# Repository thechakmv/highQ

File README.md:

# Pressure Sensor Signal Conditioning PCB

## Overview
A Schematic for the Amphenol NPH-8-200AH pressure sensor for use in aircraft systems. The circuit measures, amplifies, and filters the bridge output of the sensor to produce an analog voltage signal.

Circuit Schematic was designed to withstand noisy RF Radiation, and noise from the power of the plane itself.

## System Architecture

### Assumptions made:
- 5V & 12V Power rails
- Operating Freq ~ 30Hz (Should be sufficent for just pressure readings)

## Signal Chain

### 1. LT3092 Current Source
Current source designed to give consistent excitation current to the NPH-8-200AH
- 50ppm/C, so very temperature resistant
- Iout = 10uA * (Rset/Rout)
- R set = 15K, Rout = 100
- I out = 1.5mA

### 2. Pressue Sensor NPH-8-200AH
  Absolute pressure sensor, 0–200 PSI range
- Wheatstone bridge, 5K internal bridge resistance
  - Needs 7.5V of headroom at 1.5mA
- TO-8 package, through-hole, no bottom cylinder
- Powered via 1.5 mA constant current
- Outputs ~ 100 mV differential at 1.5 mA when excited with 10V

### 3. Input Differential RC Low Pass Filter
  Low-pass filter on differential input lines before going into the INA for RF and EMI protection
- Common Mode Cutoff frequency ~10KHz
- Differential Mode Cutoff frequency ~470Hz
- Important to have the differential cap because ceramic capacitors have up to 20% tollerance, so because the diff cap is significantly larger, it dominates and hides any discrepancies.
- R7 = R6 = 10K, C9 = C10 = 1.6nF, C18 = 16nF

### 4. REF3012 Voltage source
  Provides reference voltage to INA128 allowing us to bias the signal to 1.25V
- 50ppm/C
- Source maintains a voltage of 1.25V even through supply voltage fluctuations
- Very low output impedance
- Highly Temperature stable 

### 5. Instrumentation Amplifier, INA128
  Amplifies differential Wheatstone bridge output
- Gain set by R_G(1.6K) (pins 1 and 8): G = 1 + 50K/ 1.6K ≈ 31
- R_G value: 1.6KΩ
- REF pin set to 1.25V via REF 3012 Voltage source

### 6. Output Sallen Key Filter
  OPA188 based Sallen Key Low-pass filter after amplification
- Cutoff frequency: 40 Hz
- Due to second order falloff, provides attenuation of 40dB at 400 Hz 
- Important to block out 400Hz, because that's the frequency of Airplane AC power

## Key Design Decisions
At every point where I need to ground a component, or connect it to power, I have **Bypass Capacitors**(100nF, 10uF) to store some power, as well as preventing unwanted AC noise from the circuit.

I also installed **Ferrite Beads** to further prevent any high frequency noise from entering the circuit through the power connections.

---
---
---

# **Archive** Not relevant to current schematic, but still cool

This is archived because I unfortunately made changes to the schematic post layout in PCB

Noteable Features:
- Grounded Copper Ring surrounding circuit to protect from EMI
- Grounded Copper pours on empty space to further protect from EMI, and also to dissapate heat
- Power lines are 0.5mm and signal lines are 0.25mm
- Mounting holes are grounded to prevent further EMI, If it were to be put into production, I reccomend some kind of rubber spacer to absorb shock from the vibrations of the plane.

Noteable differences: 
- Instead of using Salen Key Filter, I used passive RC filter.
- Instead of Current Source module, I use op-amp to supply current
- Instead of Voltage Source, I used voltage divider to set Vref of the INA.

## PCB Layout
### Layer Stackup (4-layer)
| Layer | Function |
|-------|----------|
| F.Cu (Top) | Components and primary signal routing |
| In1.Cu | Solid ground plane |
| In2.Cu | Solid +5V power plane |
| B.Cu (Bottom) | Nothing |

### Noise Mitigation
- Ground plane on In1.Cu provides continuous return path and shielding
- Guard ring on F.Cu surrounds entire analog circuit, stitched to ground plane with vias
- Grounded copper fill in all empty board areas
- Input RC filter rejects RF before amplification
- Output RC filter rejects 400 Hz aircraft switching noise
- Sensitive signal traces kept narrow (0.2mm) to minimise parasitic capacitance
- Current hungry power traces kept wide (0.5mm) to maximize efficiency

### Component Selection
- All passives SMD 0603 for compactness and low parasitics
- X7R dielectric for bypass caps — stable across −40°C to 125°C
- Low TCR sense resistor (R9) for current accuracy across temperature
- INA128 Instrument Amplifier
- LM321 op-amp

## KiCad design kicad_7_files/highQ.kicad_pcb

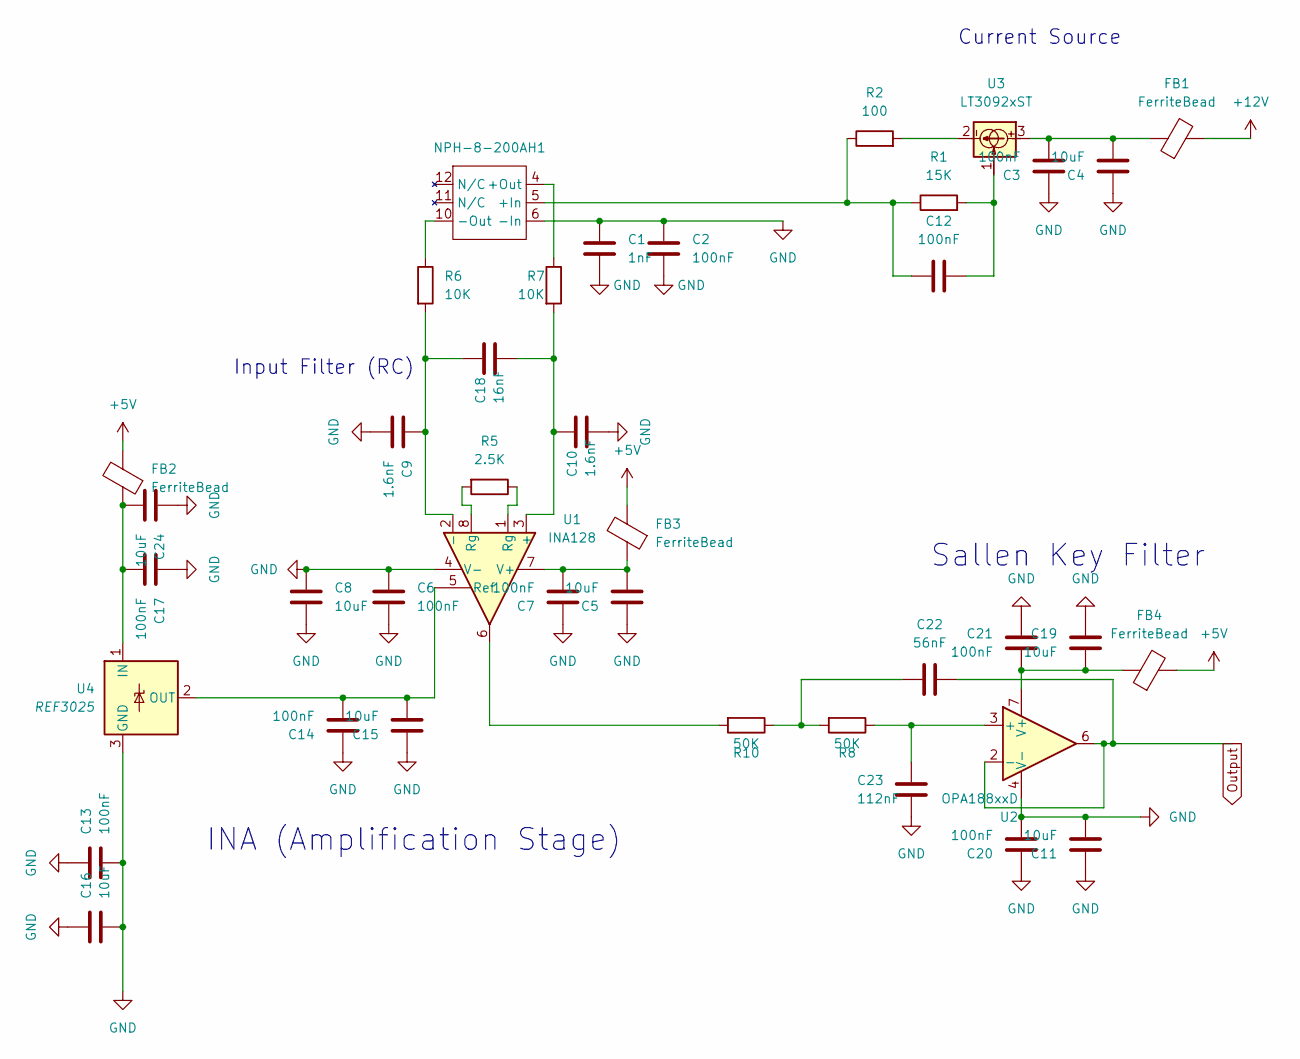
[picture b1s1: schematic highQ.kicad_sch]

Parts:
C1: 1nF; C_0603_1608Metric
C2, C3, C6, C7, C12, C13, C14, C17, C20, C21: 100nF; C_0603_1608Metric
C4, C5, C8, C11, C15, C16, C19, C24: 10uF; C_0805_2012Metric
C9, C10: 1.6nF; C_0805_2012Metric
C18: 16nF; C_0805_2012Metric
C22: 56nF; C_0603_1608Metric
C23: 112nF; C_0603_1608Metric
FB1, FB2, FB3, FB4: FerriteBead
NPH-8-200AH1: NPH-8-200AH
R1: 15K; R_0603_1608Metric
R2: 100; R_0603_1608Metric
R5: 2.5K; R_0603_1608Metric
R6, R7: 10K; R_0603_1608Metric
R8, R10: 50K; R_0603_1608Metric
U1: INA128; SOIC-8_3.9x4.9mm_P1.27mm
U2: OPA188xxD; SOIC-8_3.9x4.9mm_P1.27mm
U3: LT3092xST; SOT-223-3_TabPin2
U4: REF3025; SOT-23

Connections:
GND: C1.1, C1.2, C2.1, C2.2, C3.1, C4.1, C5.1, C6.1, C6.2, C7.1, C8.1, C8.2, C9.2, C10.2, C11.1, C11.2, C13.1, C13.2, C14.1, C15.1, C16.1, C16.2, C17.1, C19.1, C20.1, C20.2, C21.1, C23.2, C24.1, NPH-8-200AH1.6 (-In), U1.4 (V-), U2.4 (V-), U4.3 (GND)
unnamed: C3.2, C4.2, FB1.1, U3.3
unnamed: C12.2, R1.2, U3.1
unnamed: C22.1, R8.2, R10.1
unnamed: FB2.2, FB3.2, FB4.2
unnamed: C12.1, NPH-8-200AH1.5 (+In), R1.1, R2.1
unnamed: NPH-8-200AH1.4 (+Out), R7.1
unnamed: NPH-8-200AH1.10 (-Out), R6.1
unnamed: R2.2, U3.2
unnamed: R5.1, U1.1 (Rg)
unnamed: R5.2, U1.8 (Rg)
unnamed: R10.2, U1.6
unnamed: C10.1, C18.2, R7.2, U1.3 (+)
unnamed: C9.1, C18.1, R6.2, U1.2 (-)
unnamed: C14.2, C15.2, U1.5 (Ref), U4.2 (OUT)
unnamed: C5.2, C7.2, FB3.1, U1.7 (V+)
unnamed: C23.1, R8.1, U2.3 (+)
unnamed: C19.2, C21.2, FB4.1, U2.7 (V+)
unnamed: C17.2, C24.2, FB2.1, U4.1 (IN)
Output: C22.2, U2.2 (-), U2.6

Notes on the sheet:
INA (Amplification Stage)
Sallen Key Filter
Current Source
Input Filter (RC)

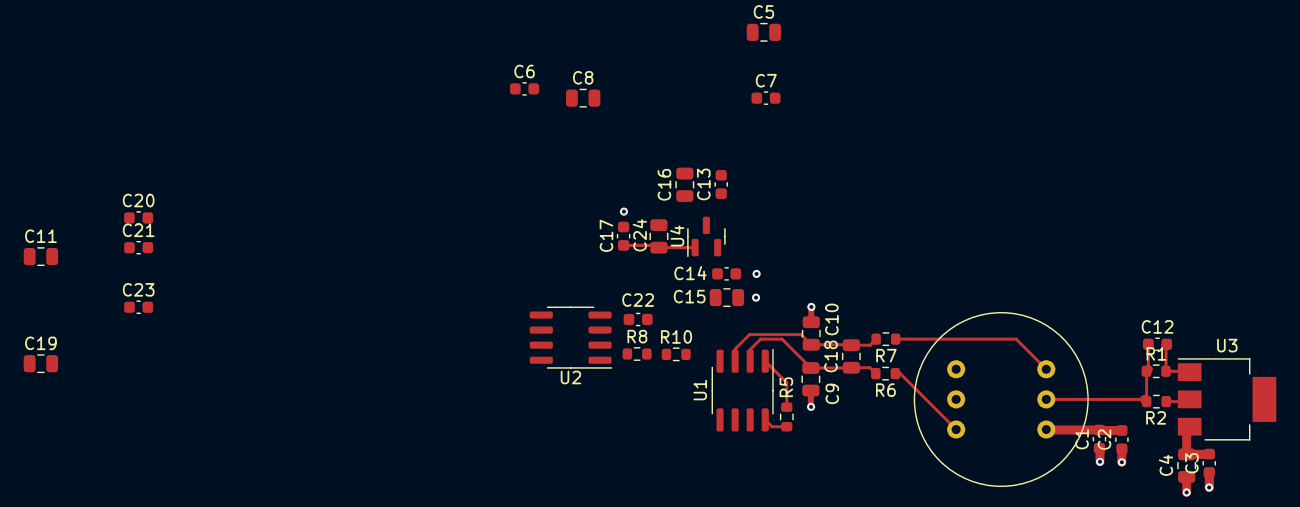
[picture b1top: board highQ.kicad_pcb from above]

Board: 4 copper layers, 36 parts (0 on the bottom side), 19 nets.

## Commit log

2026-05-26 Initialized Repo, Schematic is finished as well as README
2026-05-26 Updated Readme and Rg Value
2026-05-26 Final touches
